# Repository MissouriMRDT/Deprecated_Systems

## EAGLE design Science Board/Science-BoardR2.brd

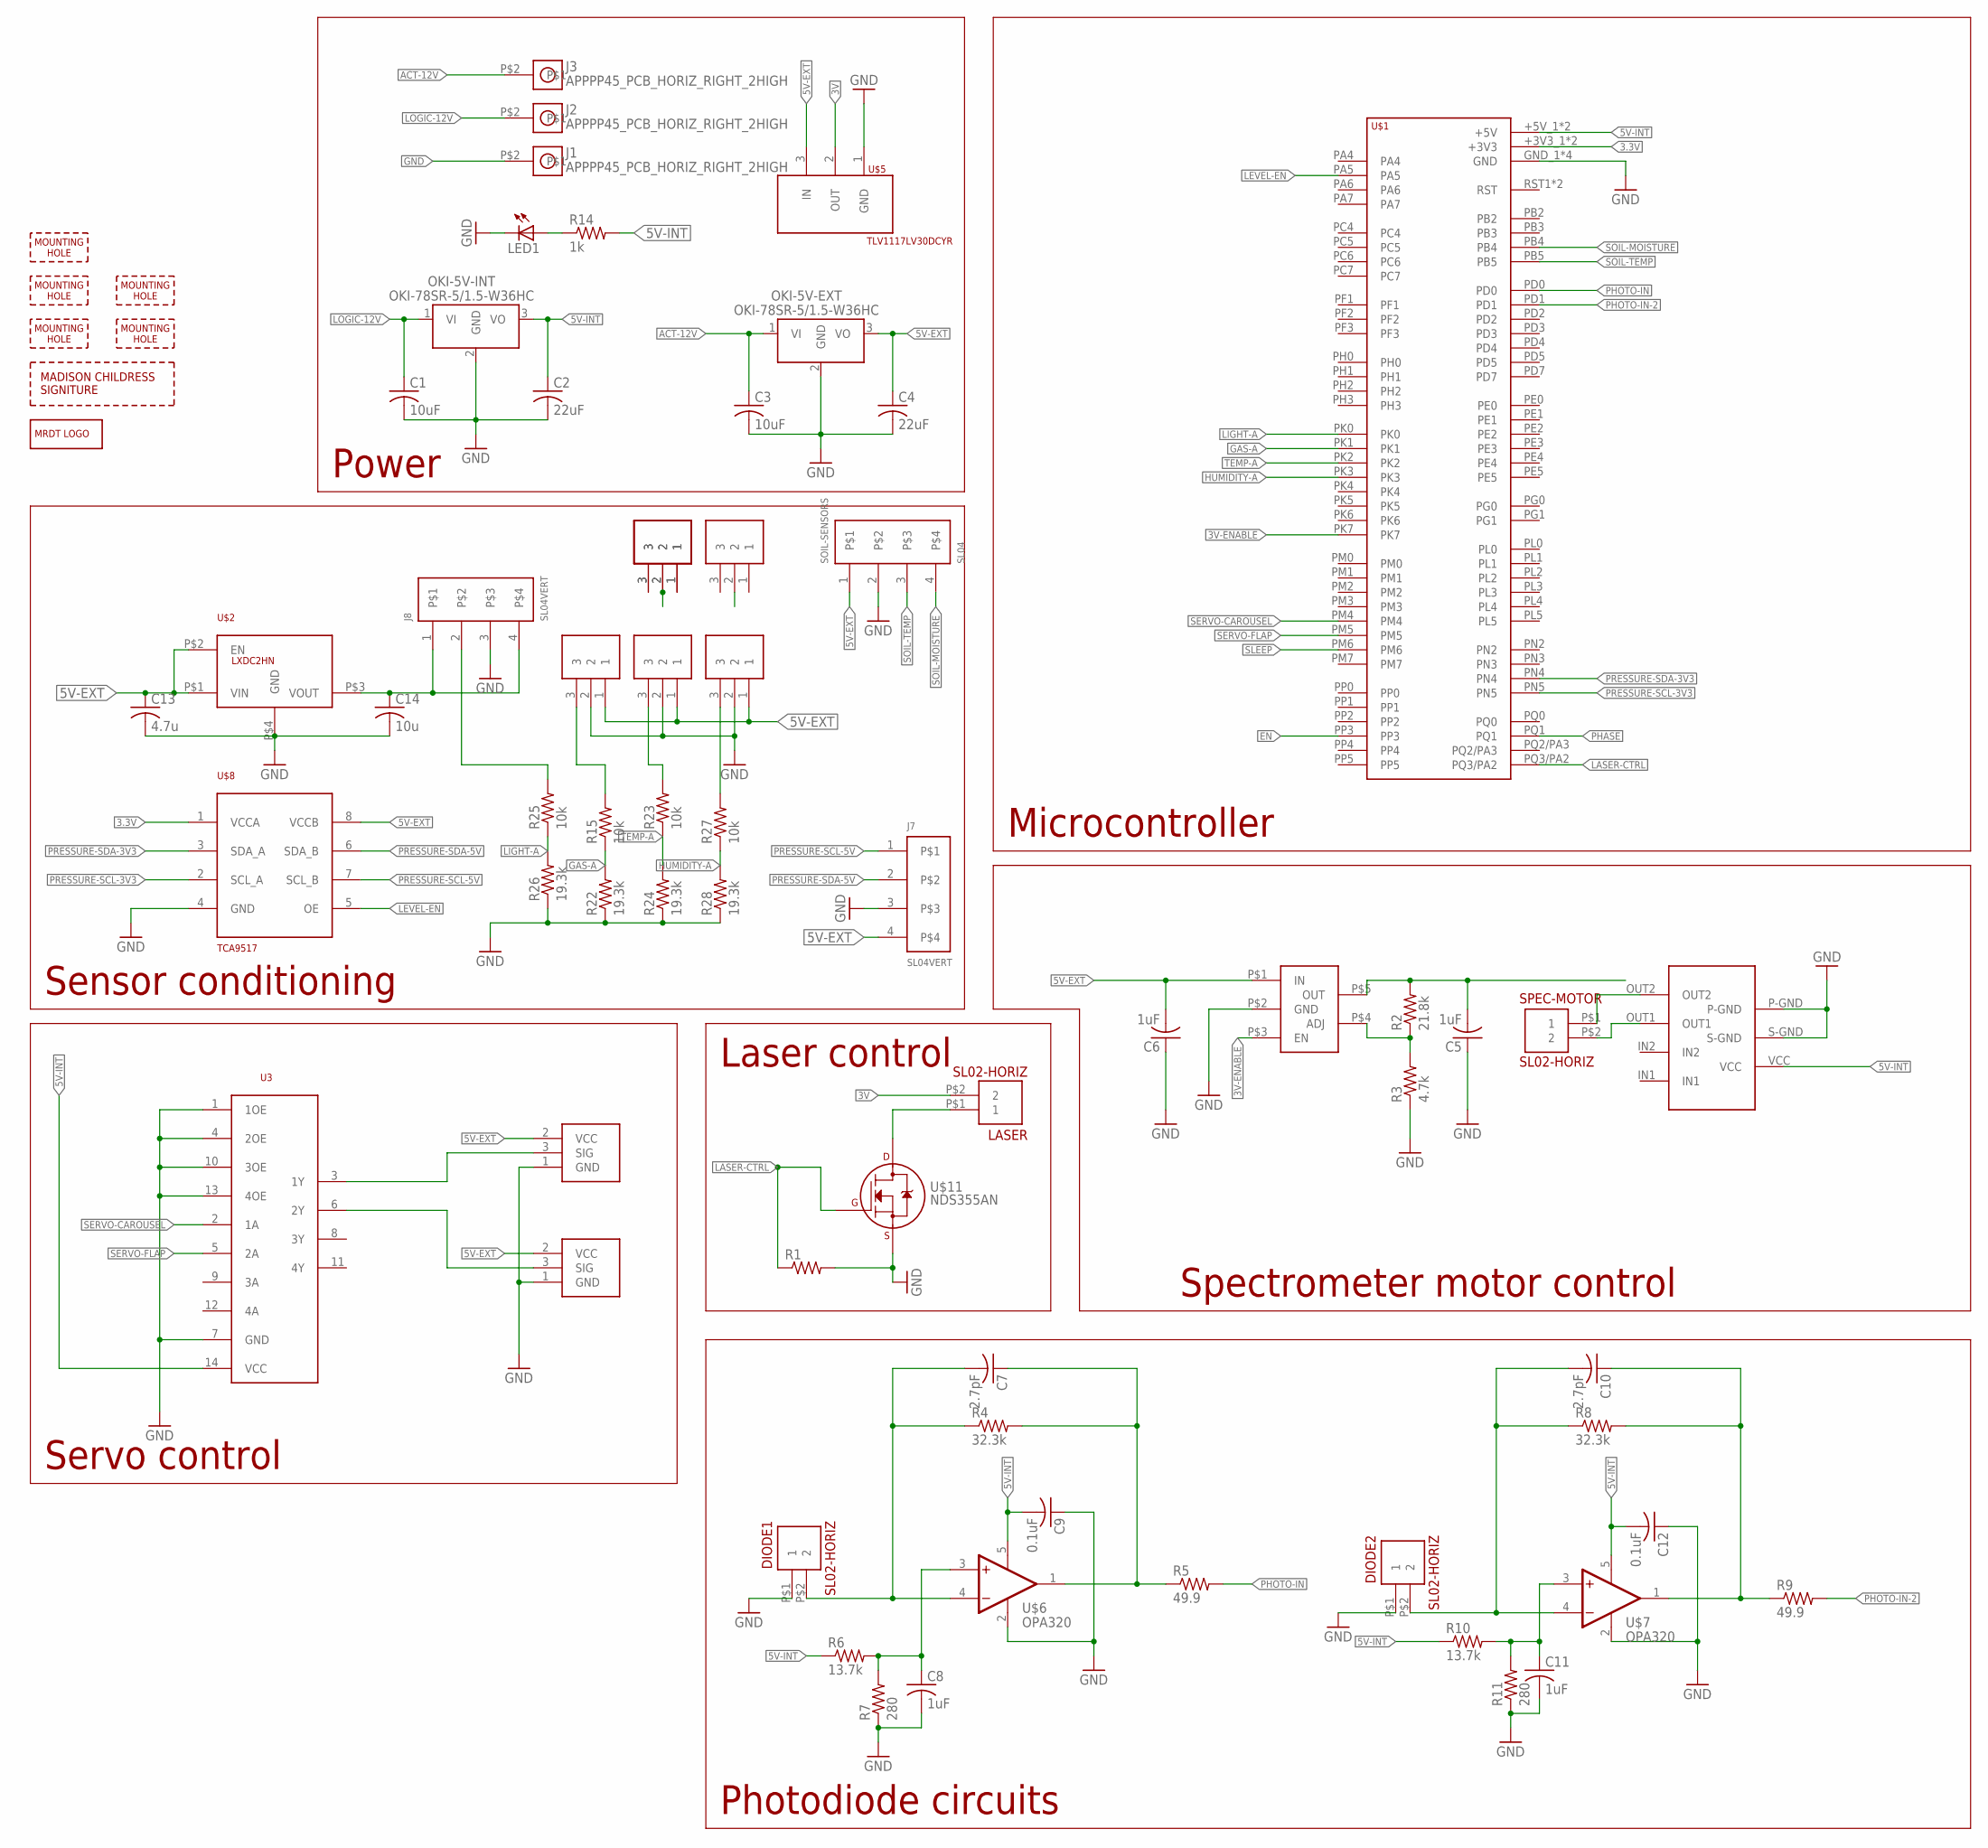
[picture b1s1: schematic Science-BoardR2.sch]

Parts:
C1, C3: 10uF; C1206
C2, C4: 22uF; C1206
C5, C6, C8, C11: 1uF; C0805
C7, C10: 2.7pF; C0805
C9, C12: 0.1uF; C0805
C13: 4.7u; C0805
C14: 10u; C0805
CAROUSEL: SERVOMOLEX_SL_THRU_HOLE; MOLEX_SL_03_TH
DIODE1, DIODE2: SL02-HORIZ; MOLEX-70551-0001
FLAP: SERVOMOLEX_SL_THRU_HOLE; MOLEX_SL_03_TH
H1, H2, H3, H4, H5: MOUNTING_HOLE#6; #6_SCREW
J1, J2, J3: APPPP45_PCB_HORIZ_RIGHT_2HIGH; APP45_PCB_HORIZ_RIGHT_2HIGH
J4, J5, J6, J9, J10, J11: SL03; MOLEX-70543-0002
J7, J8: SL04VERT; MOLEX-70543-0003
LASER: SL02-HORIZ; MOLEX-70551-0001
LED1: LEDCHIP-LED0805; CHIP-LED0805
LOGO1: MRDT_LOGO
OKI-5V-EXT, OKI-5V-INT: OKI-78SR-5/1.5-W36HC; OKI-78SR_HORIZ
R1: R-US_M0805; M0805
R2: 21.8k; M0805
R3: 4.7k; M0805
R4, R8: 32.3k; M0805
R5, R9: 49.9; M0805
R6, R10: 13.7k; M0805
R7, R11: 280; M0805
R14: 1k; M0805
R15, R23, R25, R27: 10k; R0805
R22, R24, R26, R28: 19.3k; R0805
SOIL-SENSORS: SL04; MOLEX_SL_04_TH
SPEC-MOTOR: SL02-HORIZ; MOLEX-70551-0001
U3: SN74AHCT125; SOIC14
U$1: TIVA-1294; TIVA-C-CONNECTED
U$2: LXDC2HN; 4-SMD
U$3: AP7365-WG-7DICT-ND; SOT-25
U$5: TLV1117LV30DCYR; TO-243AA
U$6, U$7: OPA320; SOT-23-5
U$8: TCA9517; SOIC8
U$9: MADISON-CHILDRESS; MADISON-CHLDRESS-SIG
U$10: LB1930MC; SOIC10
U$11: NDS355AN; SOT-23

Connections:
3.3V: U$1.+3V3_1 (+3V3), U$1.+3V3_2 (+3V3), U$8.1 (VCCA)
3V: LASER.P$2 (2), U$5.2 (OUT)
3V-ENABLE: U$1.PK7, U$3.P$3 (EN)
5V-EXT: C4.1, C6.2, C13.1, CAROUSEL.2 (VCC), FLAP.2 (VCC), J4.1, J5.1, J6.1, J7.4, OKI-5V-EXT.3 (VO), SOIL-SENSORS.1, U$2.P$1 (VIN), U$2.P$2 (EN), U$3.P$1 (IN), U$5.3 (IN), U$8.8 (VCCB)
5V-INT: C2.1, C9.2, C12.2, OKI-5V-INT.3 (VO), R6.1, R10.1, R14.2, U3.14 (VCC), U$1.+5V_1 (+5V), U$1.+5V_2 (+5V), U$6.5 (OFF1), U$7.5 (OFF1), U$10.VCC
ACT-12V: C3.1, J3.P$2, OKI-5V-EXT.1 (VI)
EN: U$1.PP3
GAS-A: R15.1, R22.2, U$1.PK1
GND: C1.2, C2.2, C3.2, C4.2, C5.1, C6.1, C8.2, C9.1, C11.2, C12.1, C13.2, C14.2, CAROUSEL.1 (GND), DIODE1.P$1 (1), DIODE2.P$1 (1), FLAP.1 (GND), J1.P$2, J4.2, J5.2, J6.2, J7.3, J8.3, LED1.C, OKI-5V-EXT.2 (GND), OKI-5V-INT.2 (GND), R1.2, R3.1, R7.1, R11.1, R22.1, R24.1, R26.1, R28.1, SOIL-SENSORS.2, U3.1 (1OE), U3.4 (2OE), U3.7 (GND), U3.10 (3OE), U3.13 (4OE), U$1.GND_1 (GND), U$1.GND_2 (GND), U$1.GND_3 (GND), U$1.GND_4 (GND), U$2.P$4 (GND), U$3.P$2 (GND), U$5.1 (GND), U$6.2 (OFF2), U$7.2 (OFF2), U$8.4 (GND), U$10.P-GND, U$10.S-GND, U$11.2 (S)
HUMIDITY-A: R27.1, R28.2, U$1.PK3
LASER-CTRL: R1.1, U$1.PQ3/PA2, U$11.1 (G)
LEVEL-EN: U$1.PA5, U$8.5 (OE)
LIGHT-A: R25.1, R26.2, U$1.PK0
LOGIC-12V: C1.1, J2.P$2, OKI-5V-INT.1 (VI)
unnamed: SPEC-MOTOR.P$1 (1), U$10.OUT2
unnamed: SPEC-MOTOR.P$2 (2), U$10.OUT1
unnamed: LASER.P$1 (1), U$11.3 (D)
unnamed: C7.2, DIODE1.P$2 (2), R4.1, U$6.4 (-IN)
unnamed: C5.2, R2.2, U$3.P$5 (OUT)
unnamed: J8.2, R25.2
unnamed: J5.3, R23.2
unnamed: C7.1, R4.2, R5.1, U$6.1 (OUT)
unnamed: C10.2, DIODE2.P$2 (2), R8.1, U$7.4 (-IN)
unnamed: C8.1, R6.2, R7.2, U$6.3 (+IN)
unnamed: CAROUSEL.3 (SIG), U3.3 (1Y)
unnamed: FLAP.3 (SIG), U3.6 (2Y)
unnamed: C10.1, R8.2, R9.1, U$7.1 (OUT)
unnamed: C11.1, R10.2, R11.2, U$7.3 (+IN)
unnamed: J9.1, J11.1
unnamed: J9.2, J11.2
unnamed: R2.1, R3.2, U$3.P$4 (ADJ)
unnamed: J9.3, J11.3
unnamed: LED1.A, R14.1
unnamed: J4.3, R15.2
unnamed: J6.3, R27.2
PHASE: U$1.PQ1
PHOTO-IN: R5.2, U$1.PD0
PHOTO-IN-2: R9.2, U$1.PD1
PRESSURE-SCL-3V3: U$1.PN5, U$8.2 (SCL_A)
PRESSURE-SCL-5V: J7.1, U$8.7 (SCL_B)
PRESSURE-SDA-3V3: U$1.PN4, U$8.3 (SDA_A)
PRESSURE-SDA-5V: J7.2, U$8.6 (SDA_B)
SERVO-CAROUSEL: U3.2 (1A), U$1.PM4
SERVO-FLAP: U3.5 (2A), U$1.PM5
SLEEP: U$1.PM6
SOIL-MOISTURE: SOIL-SENSORS.4, U$1.PB4
SOIL-TEMP: SOIL-SENSORS.3, U$1.PB5
TEMP-A: R23.1, R24.2, U$1.PK2
UV-3.3: C14.1, J8.1, J8.4, U$2.P$3 (VOUT)

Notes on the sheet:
Microcontroller
Spectrometer motor control
Photodiode circuits
Laser control
Servo control
Sensor conditioning
Power

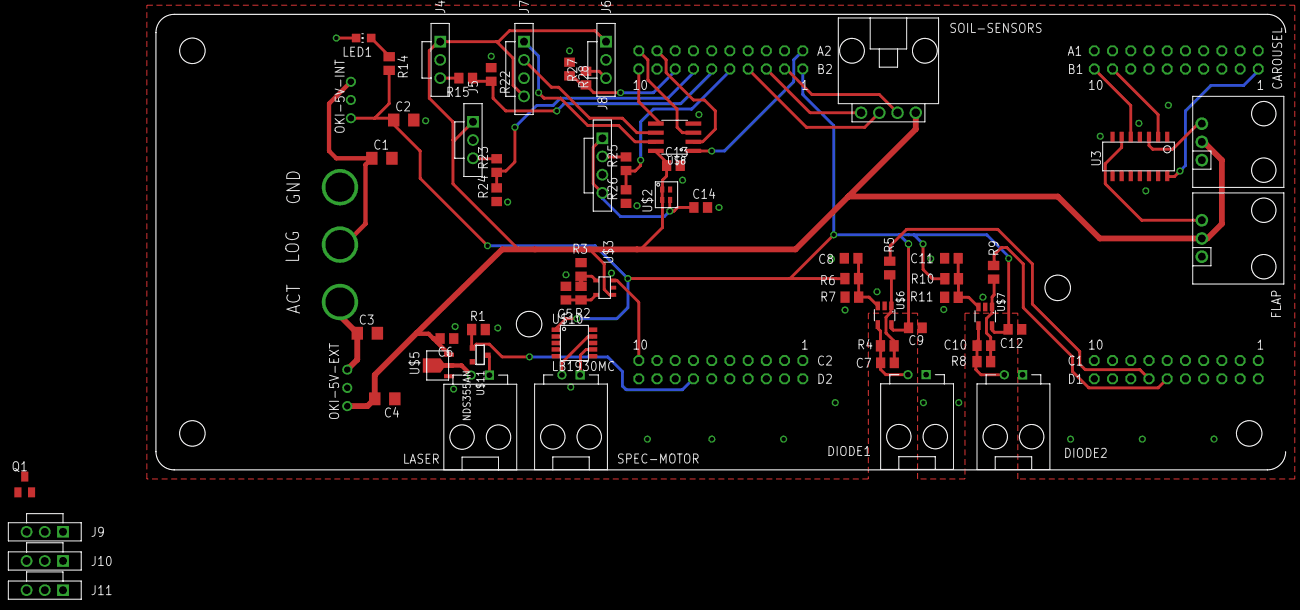
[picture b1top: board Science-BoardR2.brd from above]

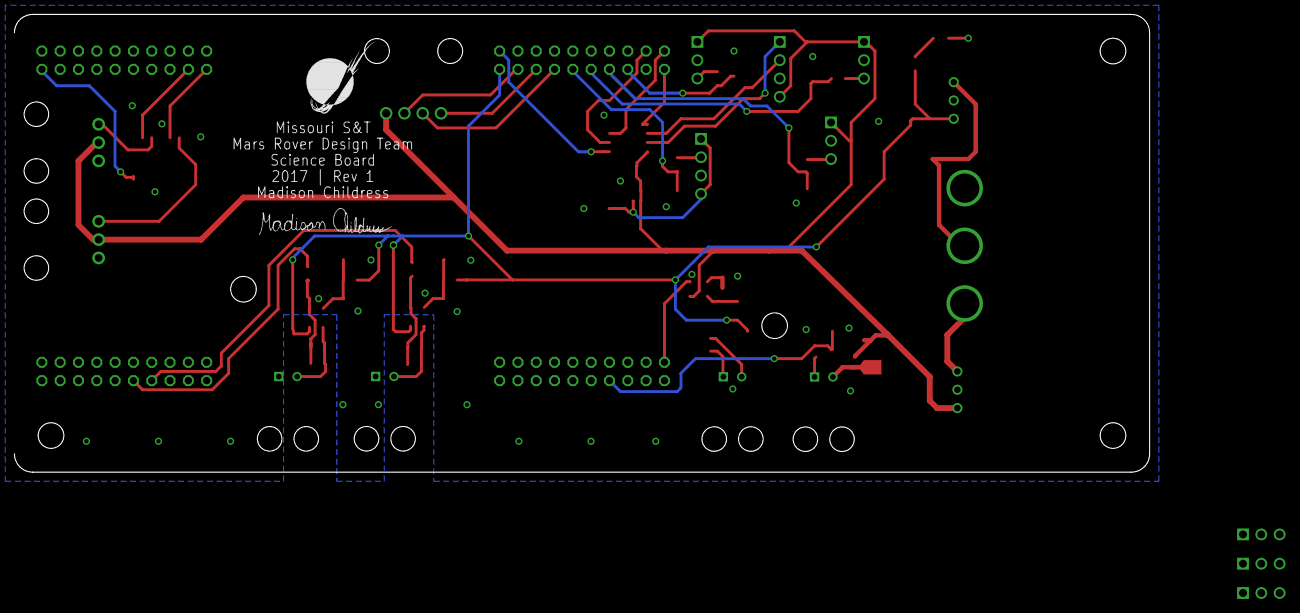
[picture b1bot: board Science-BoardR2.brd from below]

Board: 2 copper layers, 157.5 x 63.5 mm, 73 parts (2 on the bottom side), 46 nets.

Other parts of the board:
Q1: BSS123; SOT23

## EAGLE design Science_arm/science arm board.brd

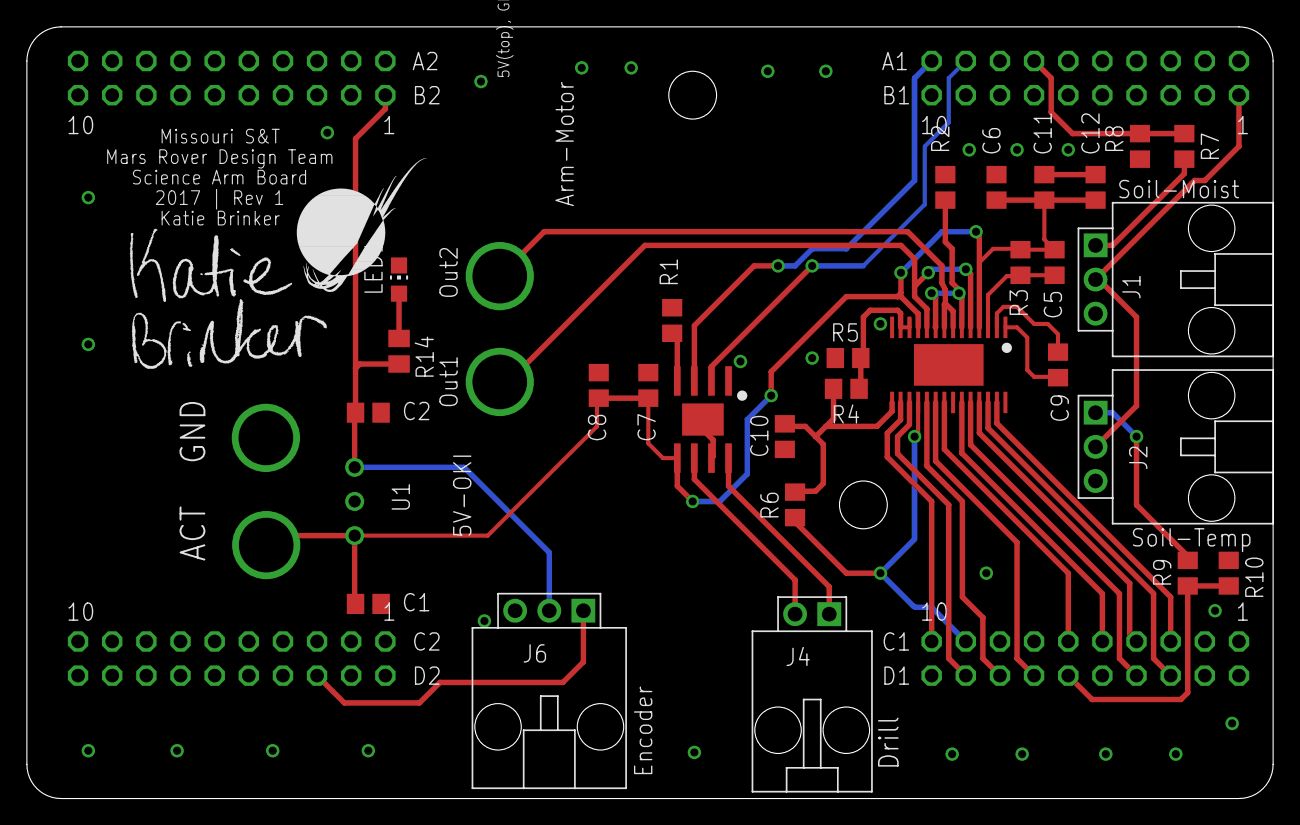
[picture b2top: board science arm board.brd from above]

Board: 2 copper layers, 92.7 x 57.4 mm, 37 parts (0 on the bottom side), 33 nets.

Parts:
ACT: APPPP45_PCB_HORIZ_RIGHT; APP45_PCB_HORIZ_RIGHT
C1: 10uF; C0805
C2: 22uF; C0805
C5, C6, C7, C12: 0.1uF; C0805
C8: 47uF; C0805
C9: 0.01uF; C0805
C10: 0.47uF; C0805
C11: 100uF; C0805
GND: APPPP45_PCB_HORIZ_RIGHT; APP45_PCB_HORIZ_RIGHT
H1, H5: MOUNTING_HOLE#6; #6_SCREW
J1, J2, J6: SL03THROUGH_HOLE; MOLEX_SL_03_TH
J3: APP_2POS_CONFIG5V_HORIZ; APP45_5V_HORIZ_CONFIG
J4: SL02-HORIZ; MOLEX-70551-0001
LED1: CHIP-LED0805
LOGO1: MRDT_LOGO
R1: 30k; R0805
R2: 100m; R0805
R3: 1M; R0805
R4: 34k; R0805
R5, R6, R7, R9: 10k; R0805
R8, R10: 19.3k; R0805
R14: 330; M0805
U1: OKI-78SR-5/1.5-W36HC; OKI-78SR_HORIZ
U$1: TIVA-1294; TIVA-C-CONNECTED
U$2: DRV8842
U$3: DRV8871
U$5: KATIE-BRINKER; KATIE-BRINKER-SIG

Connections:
3V3: C10.1, R4.2, R6.1, U$2.V3P3OUT
5V-EXT: C2.1, J1.2, J2.2, J6.2, R14.2, U1.3, U$1.+5V_1, U$1.+5V_2
12V-ACT: ACT.P$1, C1.1, C5.2, C6.1, C7.1, C8.1, C11.1, C12.1, R3.2, U1.1, U$2.VM, U$2.VM1, U$3.VM
DECAY: U$1.PN2, U$2.DECAY
ENCODER-OUT: J6.1, U$1.PP5
FAULT: R6.2, U$1.PL2, U$2.NFAULT
GND: C1.2, C2.2, C6.2, C7.2, C8.2, C10.2, C11.2, C12.2, GND.P$1, J1.3, J2.3, J6.3, LED1.C, R1.2, R2.2, R5.1, R8.1, R10.1, U1.2, U$1.GND_1, U$1.GND_2, U$1.GND_3, U$1.GND_4, U$2.GND, U$2.GND1, U$2.PPAD, U$3.GND, U$3.PGND, U$3.PPAD
I0: U$1.PL4, U$2.I0
I1: U$1.PH3, U$2.I1
I2: U$1.PG0, U$2.I2
I3: U$1.PH2, U$2.I3
I4: U$1.PF3, U$2.I4
IN1-DRILL: U$1.PB3, U$3.IN1
IN1-MAIN: U$1.PL5, U$2.IN1
IN2-DRILL: U$1.PB2, U$3.IN2
IN2-MAIN: U$1.PD0, U$2.IN2
unnamed: R1.1, U$3.ILIM
unnamed: J4.1, U$3.OUT2
unnamed: R2.1, U$2.ISEN, U$2.ISEN1
unnamed: C9.2, U$2.CP1
unnamed: C9.1, U$2.CP2
unnamed: C5.1, R3.1, U$2.VCP
unnamed: R4.1, R5.2, U$2.VREF, U$2.VREF1
unnamed: J1.1, R7.2
unnamed: J2.1, R9.2
unnamed: LED1.A, R14.1
OUT1: J4.2, U$3.OUT1
OUTPUT1: J3.5V, U$2.OUT1, U$2.OUTPUT1
OUTPUT2: J3.GND, U$2.OUT2, U$2.OUTPUT2
RESET: U$1.PL3, U$2.NRESET
SLEEP: U$1.PN3, U$2.NSLEEP
SOIL-MOIST: R7.1, R8.2, U$1.PD3
SOIL-TEMP: R9.1, R10.2, U$1.PD1

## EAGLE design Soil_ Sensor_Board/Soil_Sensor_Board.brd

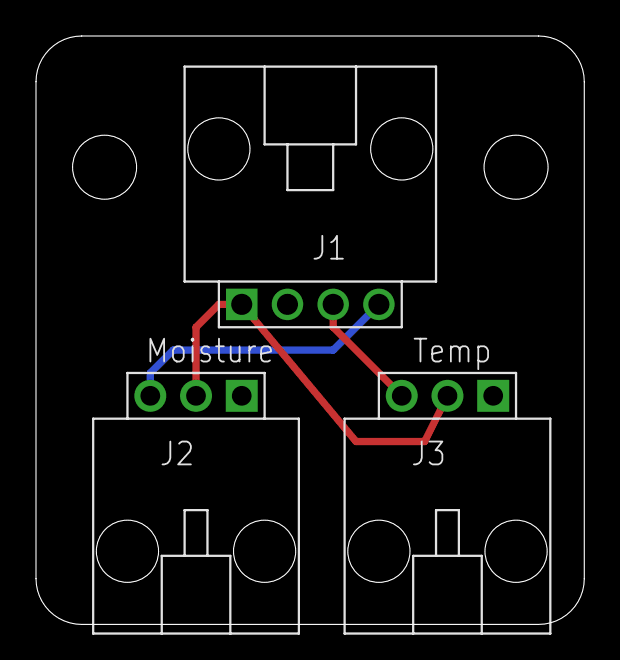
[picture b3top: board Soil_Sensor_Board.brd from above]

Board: 2 copper layers, 30.5 x 32.7 mm, 5 parts (0 on the bottom side), 4 nets.

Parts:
J1: SL04; MOLEX_SL_04_TH
J2, J3: SL03THROUGH_HOLE; MOLEX_SL_03_TH
U$1, U$2: #6_SCREW

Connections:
5V: J1.1, J2.2, J3.2
GND: J1.2, J2.1, J3.1
SOIL-MOISTURE: J1.4, J2.3
SOIL-TEMP: J1.3, J3.3

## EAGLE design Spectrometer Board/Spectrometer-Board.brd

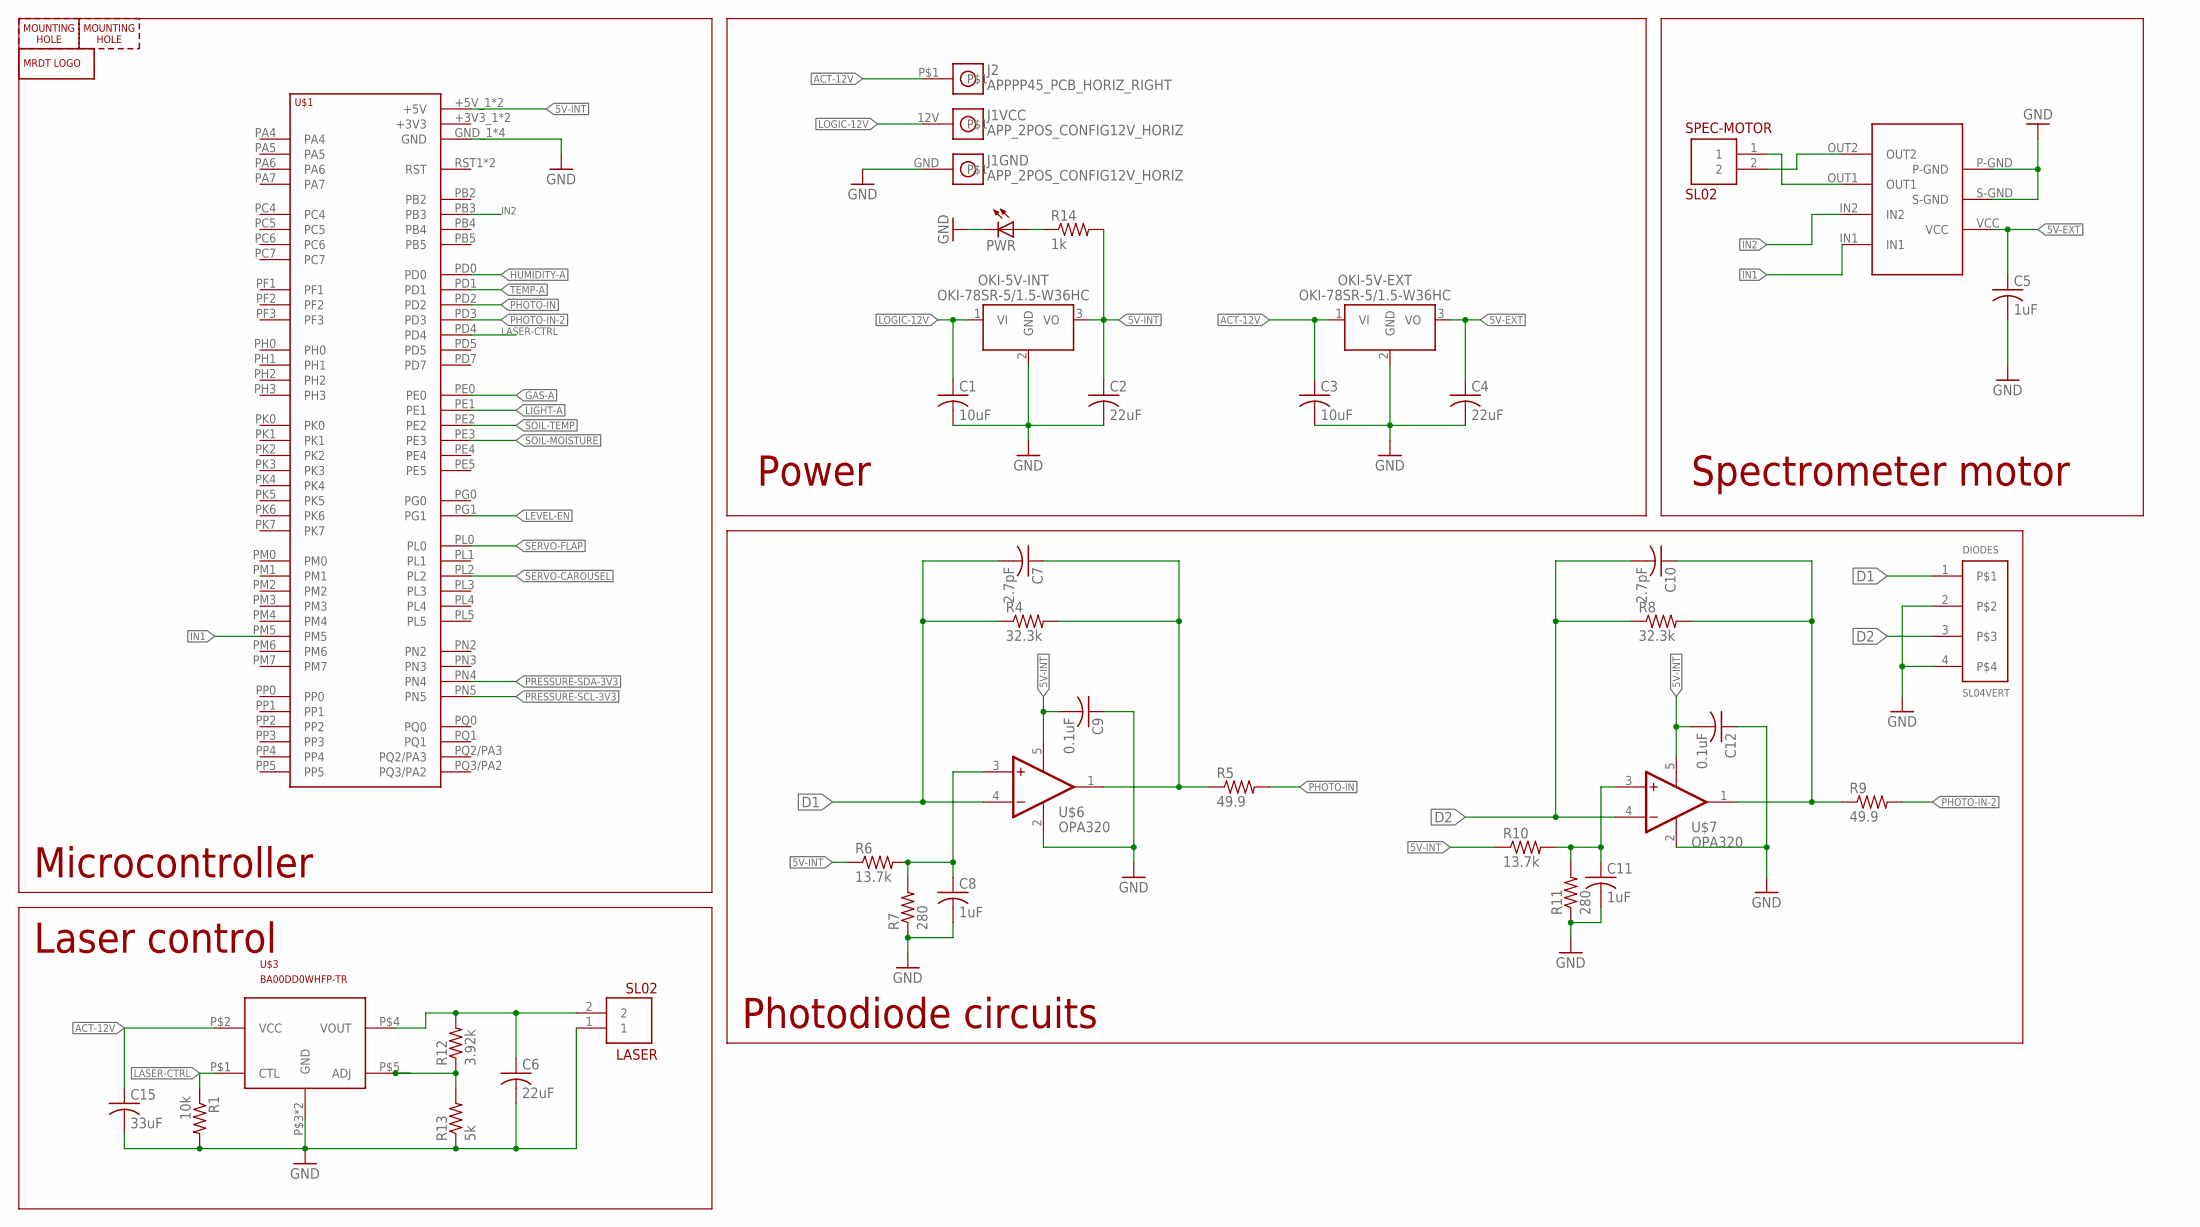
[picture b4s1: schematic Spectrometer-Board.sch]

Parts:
C1, C3: 10uF; C0805
C2, C4, C6: 22uF; C0805
C5, C8, C11: 1uF; C0805
C7, C10: 2.7pF; C0805
C9, C12: 0.1uF; C0805
C15: 33uF; C0805
DIODES: SL04VERT; MOLEX-70543-0003
H3, H4: MOUNTING_HOLE#6; #6_SCREW
J1: APP_2POS_CONFIG12V_HORIZ; APP45_12V_HORIZ_CONFIG
J2: APPPP45_PCB_HORIZ_RIGHT; APP45_PCB_HORIZ_RIGHT
LASER: SL02; MOLEX-70543-0001
LOGO1: MRDT_LOGO
OKI-5V-EXT, OKI-5V-INT: OKI-78SR-5/1.5-W36HC; OKI-78SR_HORIZ
PWR: LEDCHIP-LED0805; CHIP-LED0805
R1: 10k; M0805
R4, R8: 32.3k; M0805
R5, R9: 49.9; M0805
R6, R10: 13.7k; M0805
R7, R11: 280; M0805
R12: 3.92k; M0805
R13: 5k; M0805
R14: 1k; M0805
SPEC-MOTOR: SL02; MOLEX-70543-0001
U$1: TIVA-1294; TIVA-C-CONNECTED
U$3: BA00DD0WHFP-TR; TO-263-6
U$6, U$7: OPA320; SOT-23-5
U$10: LB1930MC; SOIC10

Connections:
5V-EXT: C4.1, C5.1, OKI-5V-EXT.3 (VO), U$10.VCC
5V-INT: C2.1, C9.2, C12.2, OKI-5V-INT.3 (VO), R6.1, R10.1, R14.2, U$1.+5V_1 (+5V), U$1.+5V_2 (+5V), U$6.5 (OFF1), U$7.5 (OFF1)
ACT-12V: C3.1, C15.1, J2.P$1, OKI-5V-EXT.1 (VI), U$3.P$2 (VCC)
D1: C7.2, DIODES.1, R4.1, U$6.4 (-IN)
D2: C10.2, DIODES.3, R8.1, U$7.4 (-IN)
GAS-A: U$1.PE0
GND: C1.2, C2.2, C3.2, C4.2, C5.2, C6.2, C8.2, C9.1, C11.2, C12.1, C15.2, DIODES.2, DIODES.4, J1.GND, LASER.1, OKI-5V-EXT.2 (GND), OKI-5V-INT.2 (GND), PWR.C, R1.2, R7.1, R11.1, R13.1, U$1.GND_1 (GND), U$1.GND_2 (GND), U$1.GND_3 (GND), U$1.GND_4 (GND), U$3.P$3 (GND), U$3.P$6 (GND), U$6.2 (OFF2), U$7.2 (OFF2), U$10.P-GND, U$10.S-GND
HUMIDITY-A: U$1.PD0
IN1: U$1.PM5, U$10.IN1
IN2: U$1.PB3, U$10.IN2
LASER-CTRL: R1.1, U$1.PD4, U$3.P$1 (CTL)
LEVEL-EN: U$1.PG1
LIGHT-A: U$1.PE1
LOGIC-12V: C1.1, J1.12V, OKI-5V-INT.1 (VI)
unnamed: SPEC-MOTOR.2, U$10.OUT2
unnamed: SPEC-MOTOR.1, U$10.OUT1
unnamed: C6.1, LASER.2, R12.2, U$3.P$4 (VOUT)
unnamed: C7.1, R4.2, R5.1, U$6.1 (OUT)
unnamed: C8.1, R6.2, R7.2, U$6.3 (+IN)
unnamed: C10.1, R8.2, R9.1, U$7.1 (OUT)
unnamed: C11.1, R10.2, R11.2, U$7.3 (+IN)
unnamed: PWR.A, R14.1
unnamed: R12.1, R13.2, U$3.P$5 (ADJ)
PHOTO-IN: R5.2, U$1.PD2
PHOTO-IN-2: R9.2, U$1.PD3
PRESSURE-SCL-3V3: U$1.PN5
PRESSURE-SDA-3V3: U$1.PN4
SERVO-CAROUSEL: U$1.PL2
SERVO-FLAP: U$1.PL0
SOIL-MOISTURE: U$1.PE3
SOIL-TEMP: U$1.PE2
TEMP-A: U$1.PD1

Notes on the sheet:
Microcontroller
Spectrometer motor
Photodiode circuits
Laser control
Power

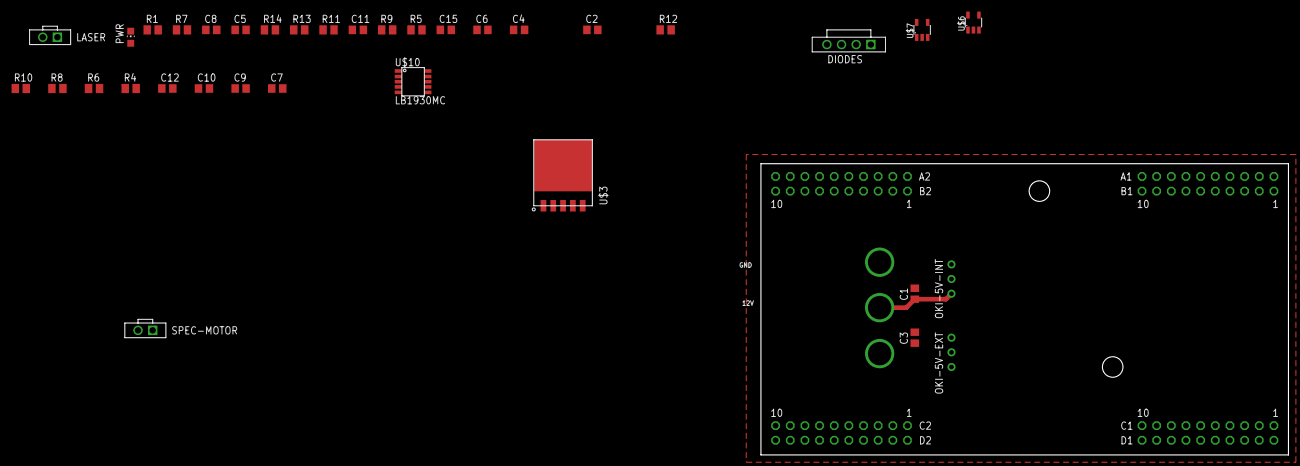
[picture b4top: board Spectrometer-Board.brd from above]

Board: 2 copper layers, 91.4 x 50.5 mm, 41 parts (0 on the bottom side), 21 nets.

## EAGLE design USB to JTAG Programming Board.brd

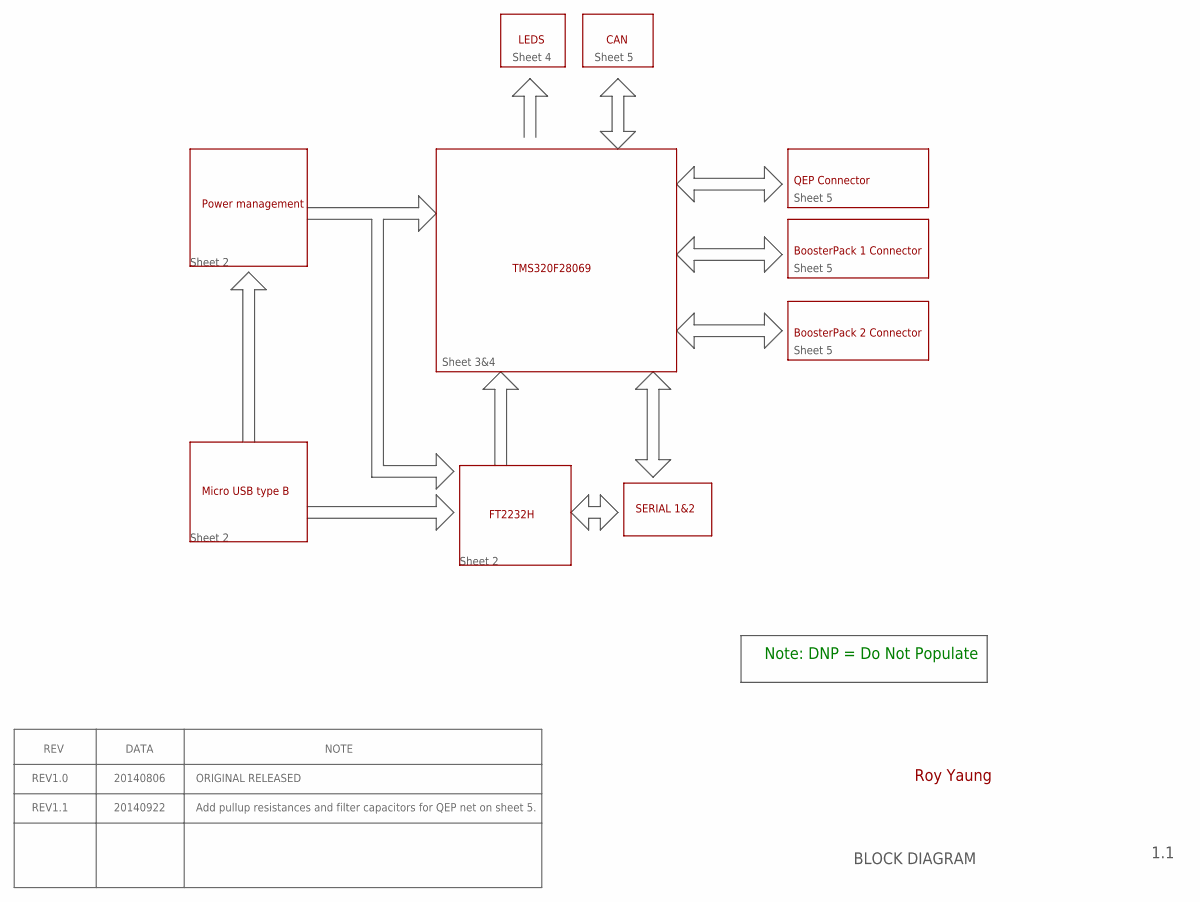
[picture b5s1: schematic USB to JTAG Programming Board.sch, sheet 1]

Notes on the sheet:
1.1
BLOCK DIAGRAM
Power management
Micro USB type B
FT2232H
TMS320F28069
BoosterPack 1 Connector
LEDS
CAN
SERIAL 1&2
Sheet 2
Sheet 3&4
BoosterPack 2 Connector
QEP Connector
Note: DNP = Do Not Populate
Roy Yaung
Sheet 5
Sheet 4
REV
DATA
NOTE
REV1.0
REV1.1
20140806
20140922
ORIGINAL RELEASED
Add pullup resistances and filter capacitors for QEP net on sheet 5.

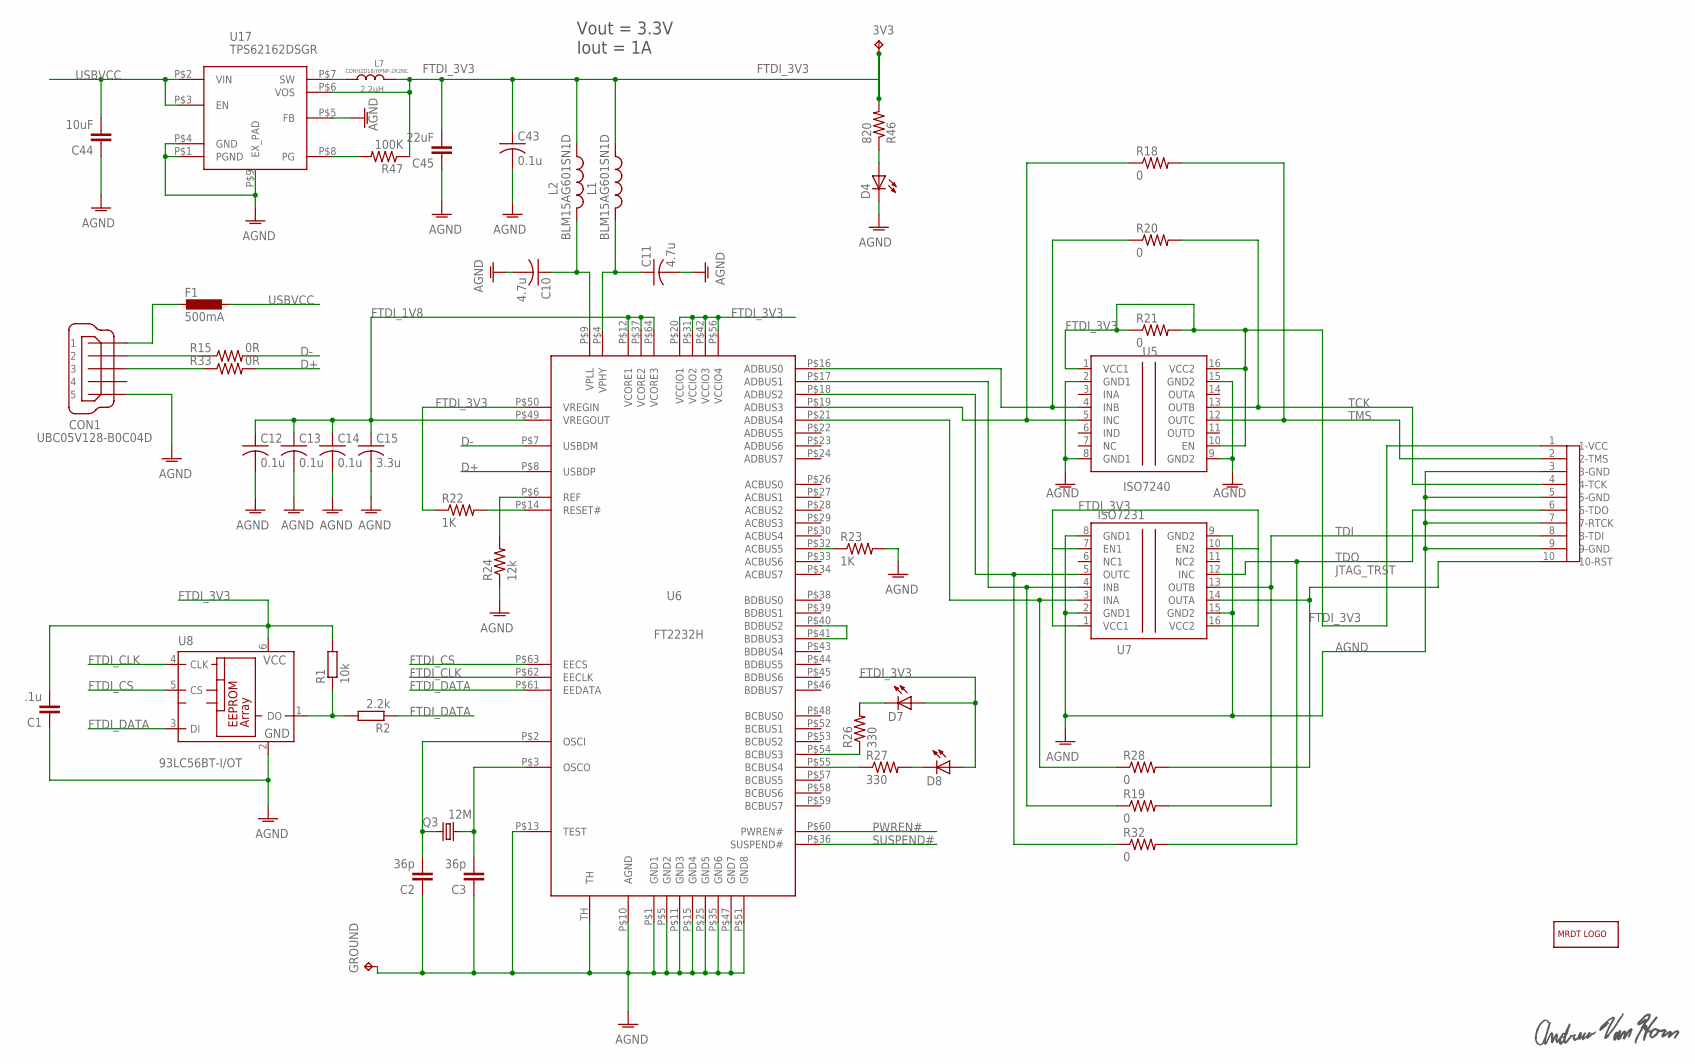
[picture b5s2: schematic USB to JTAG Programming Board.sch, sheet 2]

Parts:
3V3: TESTPAD_TPB1,27; TESTPAD_B1,27
C1: .1u; C0603
C2, C3: 36p; C0603
C10, C11: 4.7u; C0402
C12, C13, C14, C43: 0.1u; C0402
C15: 3.3u; C0402
C44: 10uF; SPARKFUN_1210
C45: 22uF; SPARKFUN_1210
CON1: UBC05V128-B0C04D; 32005-201
D4, D7, D8: LEDCHIP-LED0603; CHIP-LED0603
F1: 500mA; L1812
GROUND: TESTPAD_TPB1,27; TESTPAD_B1,27
L1, L2: BLM15AG601SN1D; R0402
L7: 2.2uH; INDUCT-3.2*3.2
LOGO1: MRDT_LOGO
Q3: 12M; HC49UP
R1: 10k; R0603
R2: 2.2k; R0603
R15, R33: 0R; R0402
R18, R19, R20, R21, R28, R32: 0; R1206
R22, R23: 1K; R0402
R24: 12k; R0402
R26, R27: 330; R0402
R46: 820; R0402
R47: 100K; R0402
U5: ISO7240; SO-16DW
U6: FT2232H; QFN64
U7: ISO7231; SO-16DW
U8: 93LC56BT-I/OT; SOT23-6
U17: TPS62162DSGR; TI_DSG8
U$1: IDC_BOX_HEADER_2X5_1.27MM; 1.27MM_2X5_BOX_HEADER_STRAIGHT
U$2: ANDREW_VAN_HORN_SIGNATURE

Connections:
AGND: C1.1, C2.1, C3.1, C10.2, C11.2, C12.2, C13.2, C14.2, C15.2, C43.2, C44.1, C45.1, CON1.5, D4.C, GROUND.TP, R23.2, R24.1, U5.2 (GND1), U5.8 (GND1), U5.9 (GND2), U5.15 (GND2), U6.P$1 (GND1), U6.P$5 (GND2), U6.P$10 (AGND), U6.P$11 (GND3), U6.P$13 (TEST), U6.P$15 (GND4), U6.P$25 (GND5), U6.P$35 (GND6), U6.P$47 (GND7), U6.P$51 (GND8), U6.TH, U7.2 (GND1), U7.8 (GND1), U7.9 (GND2), U7.15 (GND2), U8.2 (GND), U17.P$1 (PGND), U17.P$4 (GND), U17.P$5 (FB), U17.P$9 (EX_PAD), U$1.3 (3-GND), U$1.5 (5-GND), U$1.7 (7-RTCK), U$1.9 (9-GND)
D+: R33.2, U6.P$8 (USBDP)
D-: R15.2, U6.P$7 (USBDM)
FTDI_1V8: C12.1, C13.1, C14.1, C15.1, U6.P$12 (VCORE1), U6.P$37 (VCORE2), U6.P$49 (VREGOUT), U6.P$64 (VCORE3)
FTDI_3V3: 3V3.TP, C1.2, C43.1, C45.2, D7.A, D8.A, L1.1, L2.1, L7.P$1 (1), R1.2, R21.1, R21.2, R22.1, R46.2, R47.1, U5.1 (VCC1), U5.10 (EN), U5.16 (VCC2), U6.P$20 (VCCIO1), U6.P$31 (VCCIO2), U6.P$42 (VCCIO3), U6.P$50 (VREGIN), U6.P$56 (VCCIO4), U7.1 (VCC1), U7.7 (EN1), U7.10 (EN2), U7.16 (VCC2), U8.6 (VCC), U17.P$6 (VOS), U$1.1 (1-VCC)
FTDI_CLK: U6.P$62 (EECLK), U8.4 (CLK)
FTDI_CS: U6.P$63 (EECS), U8.5 (CS)
FTDI_DATA: R2.1, U6.P$61 (EEDATA), U8.3 (DI)
JTAG_TRST: R28.2, U7.14 (OUTA), U$1.10 (10-RST)
unnamed: R20.1, U5.4 (INB), U6.P$16 (ADBUS0)
unnamed: C2.2, Q3.1, U6.P$2 (OSCI)
unnamed: R19.1, U6.P$17 (ADBUS1), U7.4 (INB)
unnamed: R32.1, U6.P$18 (ADBUS2), U7.5 (OUTC)
unnamed: R18.1, U5.5 (INC), U6.P$19 (ADBUS3)
unnamed: C3.2, Q3.2, U6.P$3 (OSCO)
unnamed: R1.1, R2.2, U8.1 (DO)
unnamed: R28.1, U6.P$21 (ADBUS4), U7.3 (INA)
unnamed: R23.1, U6.P$32 (ACBUS5)
unnamed: U6.P$40 (BDBUS2), U6.P$41 (BDBUS3)
unnamed: R24.2, U6.P$6 (REF)
unnamed: R26.1, U6.P$54 (BCBUS3)
unnamed: C11.1, L1.2, U6.P$4 (VPHY)
unnamed: R27.1, U6.P$55 (BCBUS4)
unnamed: D7.C, R26.2
unnamed: D8.C, R27.2
unnamed: C10.1, L2.2, U6.P$9 (VPLL)
unnamed: R22.2, U6.P$14 (RESET#)
unnamed: CON1.2, R15.1
unnamed: CON1.3, R33.1
unnamed: D4.A, R46.1
unnamed: R47.2, U17.P$8 (PG)
unnamed: L7.P$2 (2), U17.P$7 (SW)
PWREN#: U6.P$60 (PWREN#)
SUSPEND#: U6.P$36 (SUSPEND#)
TCK: R20.2, U5.13 (OUTB), U$1.4 (4-TCK)
TDI: R19.2, U7.13 (OUTB), U$1.8 (8-TDI)
TDO: R32.2, U7.12 (INC), U$1.6 (6-TDO)
TMS: R18.2, U5.12 (OUTC), U$1.2 (2-TMS)
USBVCC: C44.2, F1.1, U17.P$2 (VIN), U17.P$3 (EN)
XUSB: CON1.1, F1.2

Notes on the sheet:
Vout = 3.3V
Iout = 1A
CDRH2D18/HPNP-2R2NC

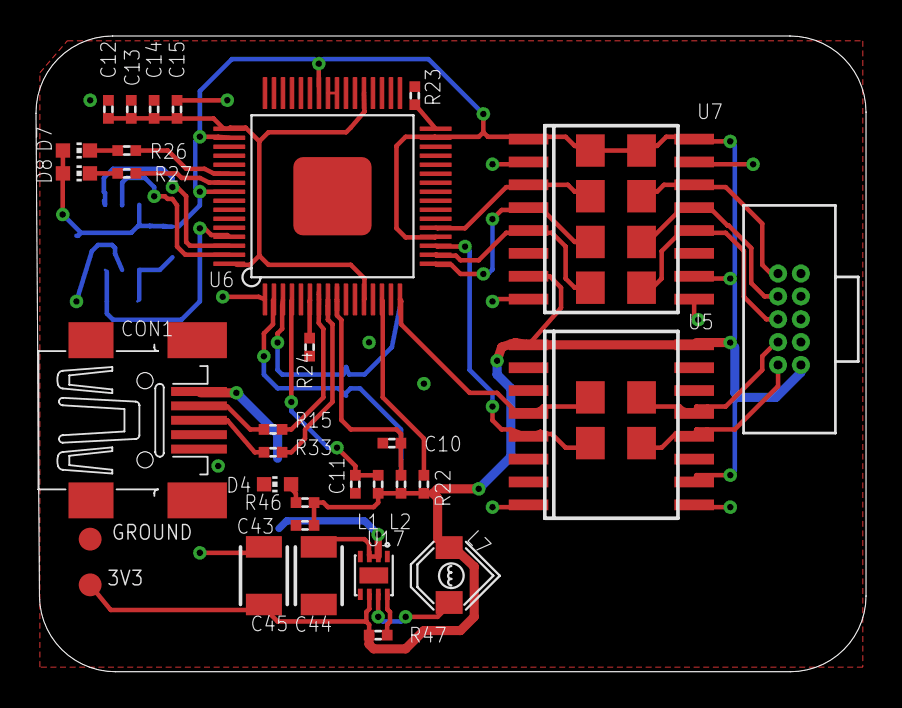
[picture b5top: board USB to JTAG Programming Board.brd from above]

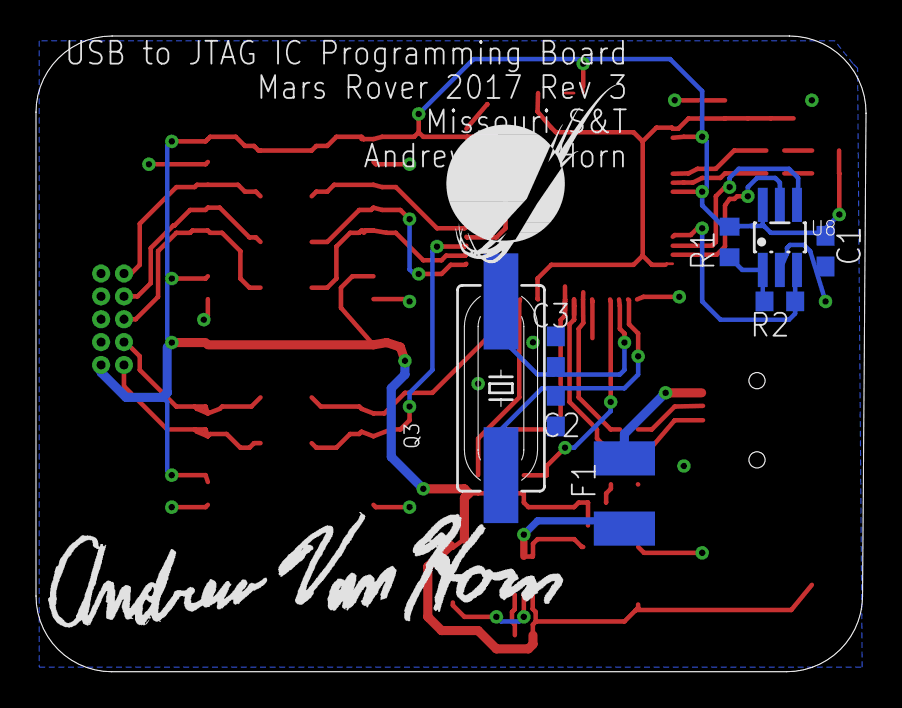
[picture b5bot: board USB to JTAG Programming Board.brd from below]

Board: 2 copper layers, 46.1 x 35.3 mm, 48 parts (10 on the bottom side), 38 nets.

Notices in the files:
parts and their libraries:
SparkFun-Aesthetics: Licensing: CC v3.0 Share-Alike You are welcome to use this library for commercial purposes.
LilyPad-Wearables: Licensing:Creative Commons ShareAlike 4.0 International - https://creativecommons.org/licenses/by-sa/4.0
